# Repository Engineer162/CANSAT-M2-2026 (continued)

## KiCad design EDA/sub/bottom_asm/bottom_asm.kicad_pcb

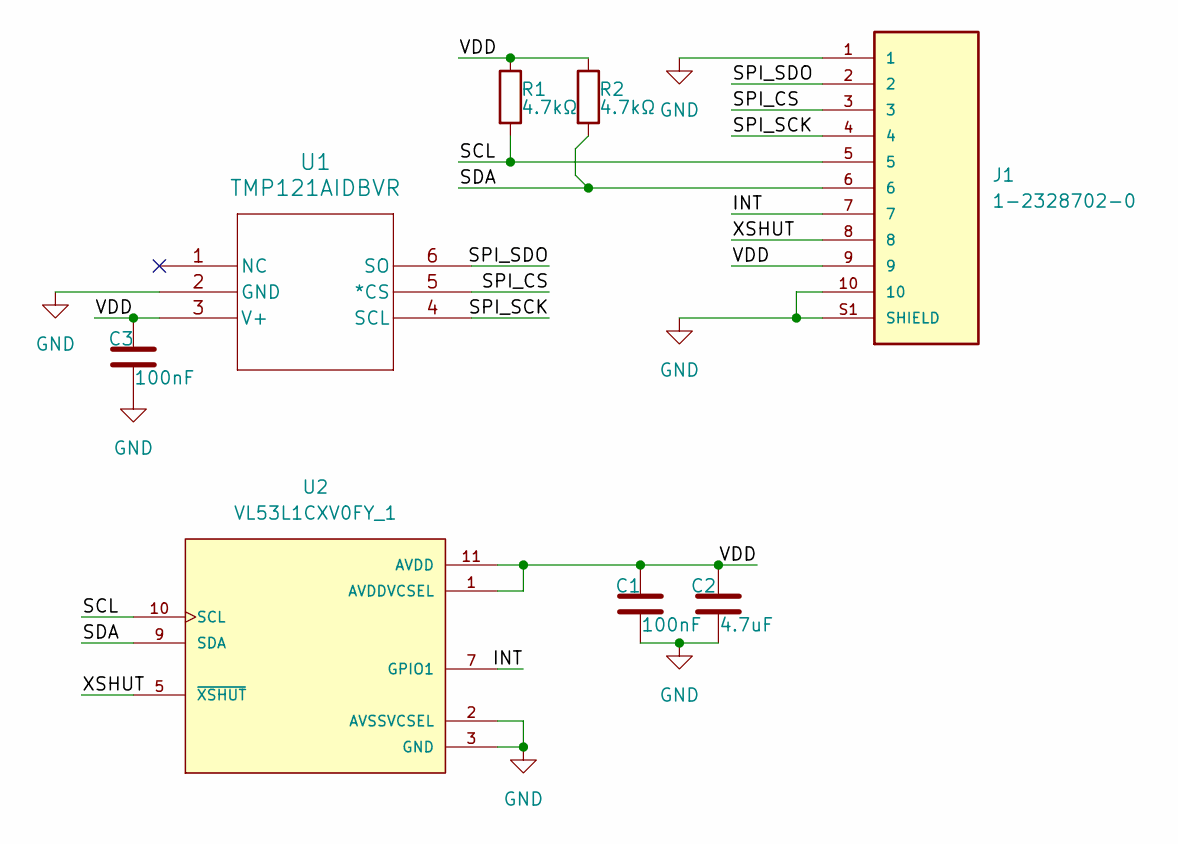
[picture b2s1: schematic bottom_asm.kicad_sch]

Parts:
C1, C3: 100nF; C_0402_1005Metric; Manufacturer Part CL05B104KP5NNNC
C2: 4.7uF; C_0603_1608Metric; Manufacturer Part CL10A475KP8NNNC
J1: 1-2328702-0; TE_1-2328702-0; PARTREV 5; DigiKey_Part_Number A141390CT-ND
R1, R2: 4.7kΩ; R_0402_1005Metric; Manufacturer Part RC0402JR-074K7L
U1: TMP121AIDBVR; DBV6; Manufacturer Part TMP121AIDBVR
U2: VL53L1CXV0FY_1; SENSOR_VL53L1CXV0FY_1; PARTREV 2

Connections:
/INT: J1.7, U2.7 (GPIO1)
/SCL: J1.5, R1.2, U2.10 (SCL)
/SDA: J1.6, R2.2, U2.9 (SDA)
/SPI_CS: J1.3, U1.5 (*CS)
/SPI_SCK: J1.4, U1.4 (SCL)
/SPI_SDO: J1.2, U1.6 (SO)
/VDD: C1.1, C2.1, C3.1, J1.9, R1.1, R2.1, U1.3 (V+), U2.1 (AVDDVCSEL), U2.11 (AVDD)
/XSHUT: J1.8, U2.5 (~XSHUT)
GND: C1.2, C2.2, C3.2, J1.1, J1.10, J1.S1 (SHIELD), J1.S2 (SHIELD), U1.2 (GND), U2.2 (AVSSVCSEL), U2.3 (GND), U2.4 (GND), U2.6 (GND), U2.12 (GND)

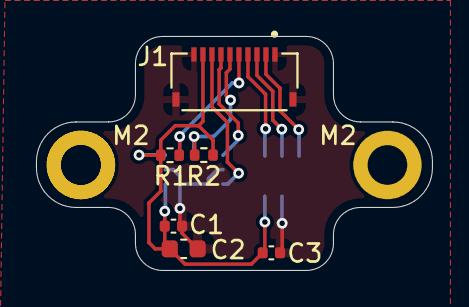
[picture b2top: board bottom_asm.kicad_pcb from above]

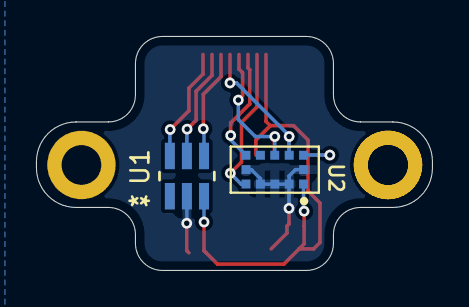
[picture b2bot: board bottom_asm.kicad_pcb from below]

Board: 2 copper layers, 22.0 x 13.0 mm, 10 parts (2 on the bottom side), 9 nets.

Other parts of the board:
M2, M2#2: MountingHole_2.2mm_M2_DIN965_Pad

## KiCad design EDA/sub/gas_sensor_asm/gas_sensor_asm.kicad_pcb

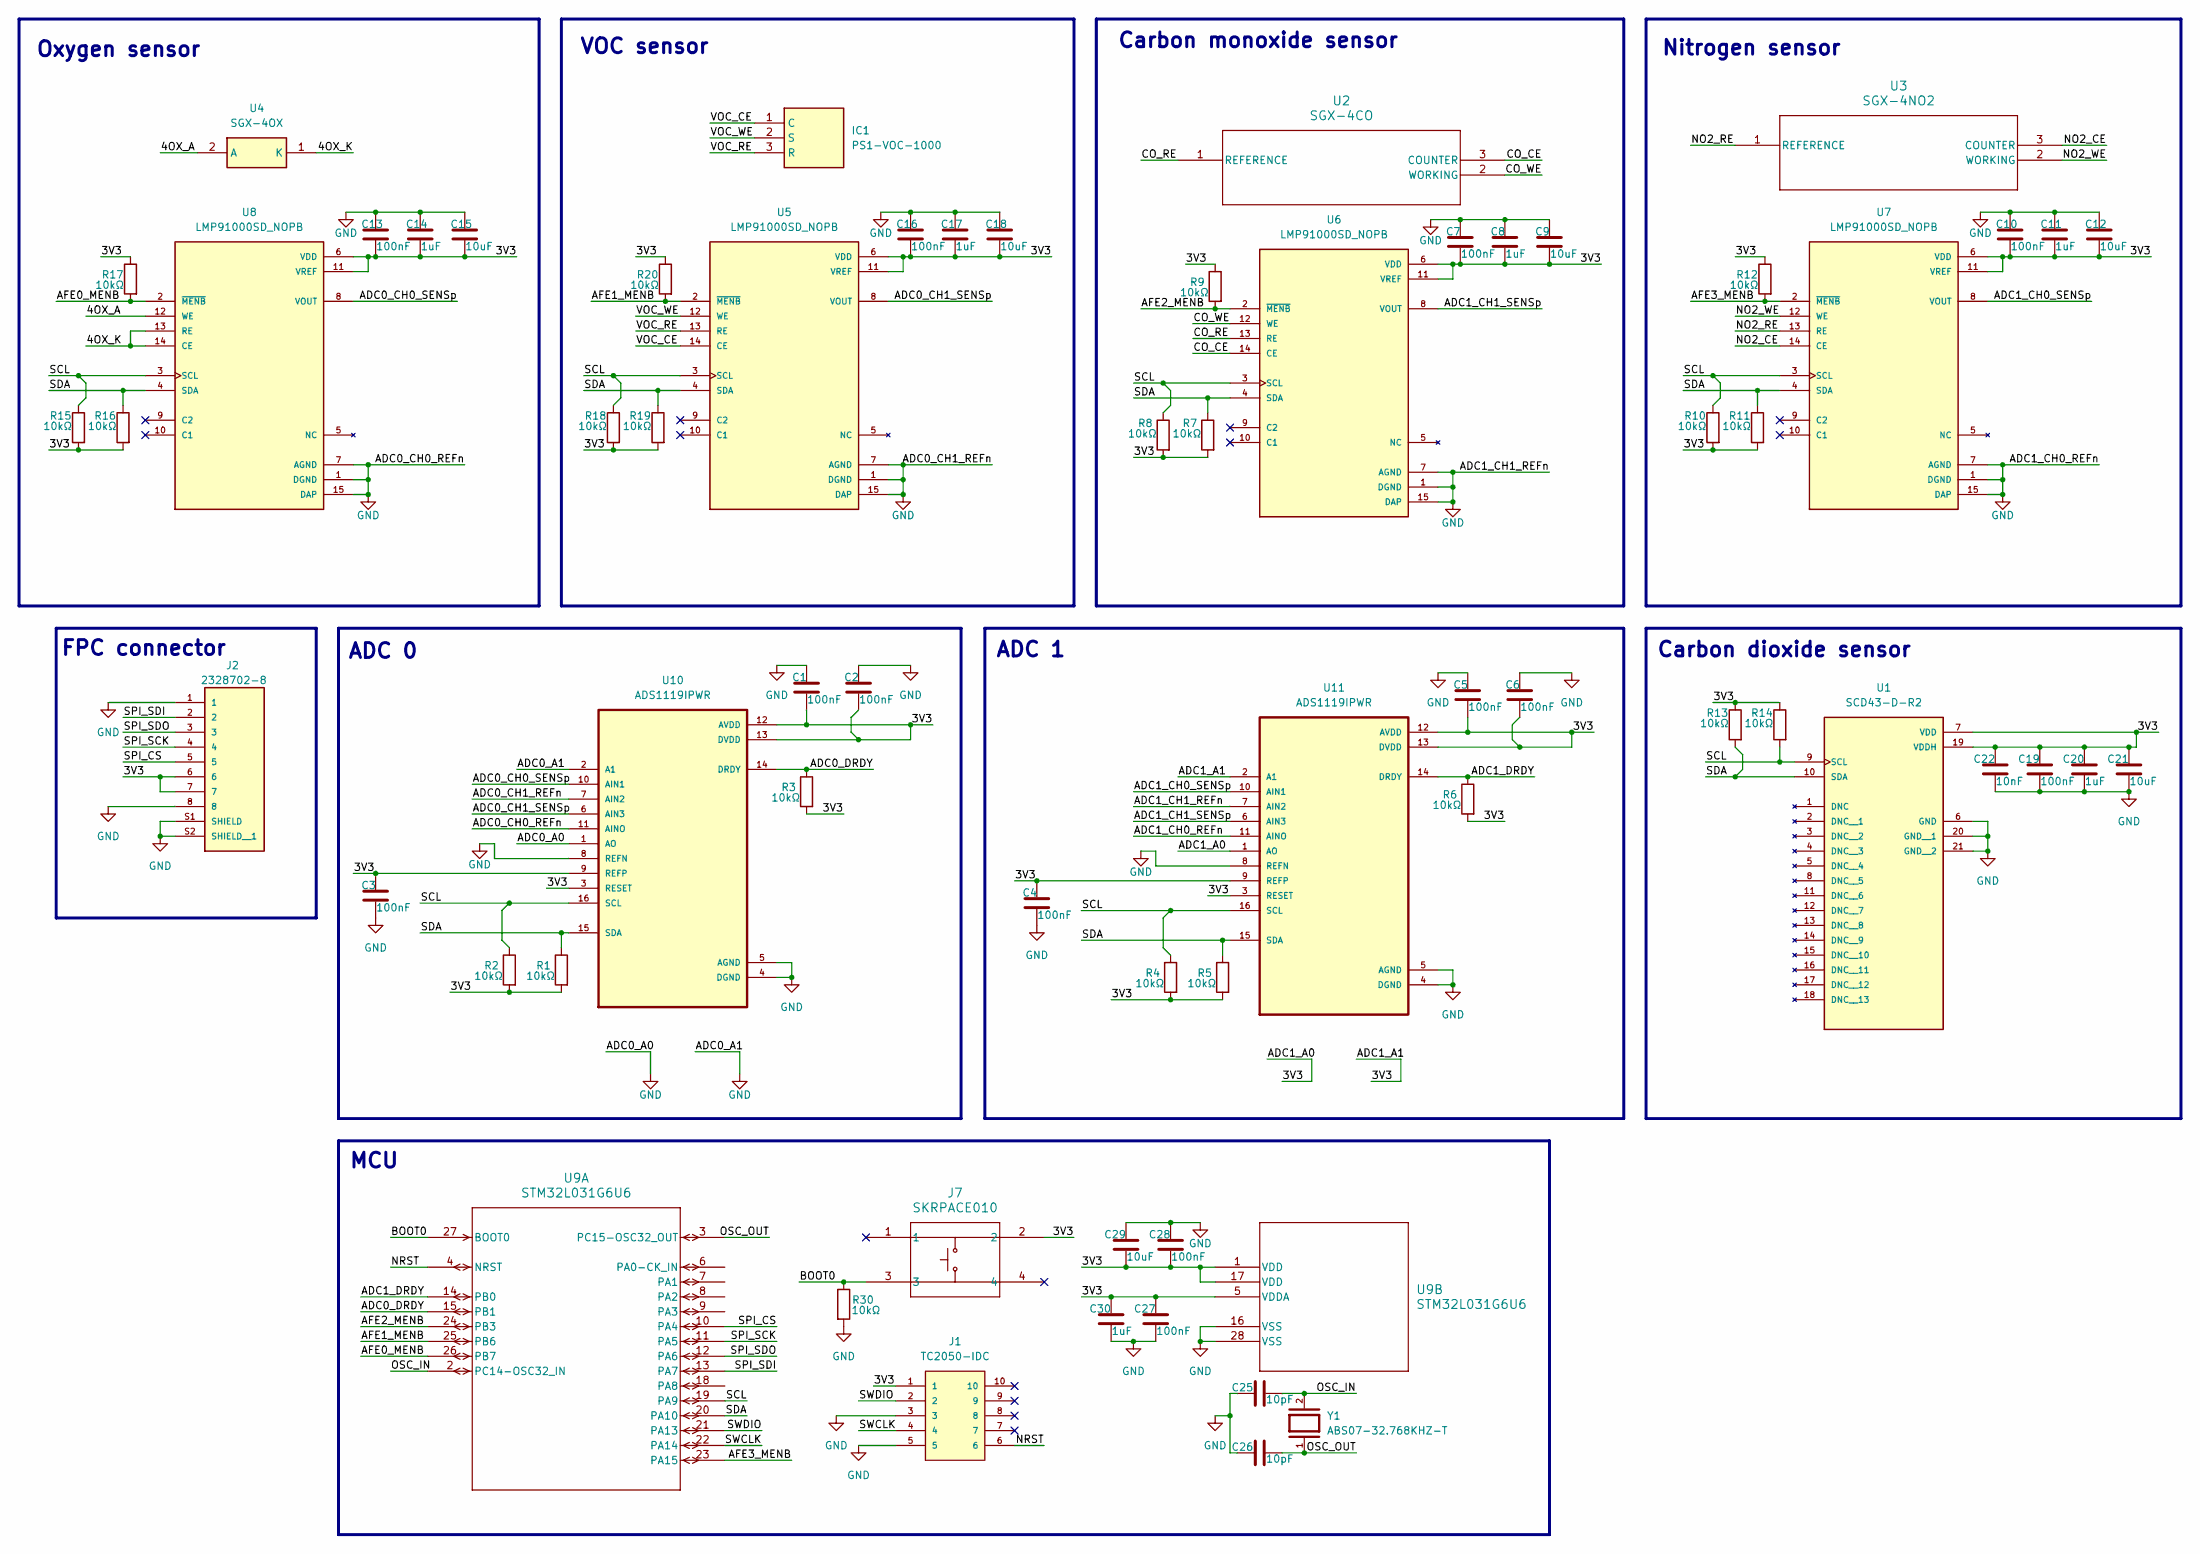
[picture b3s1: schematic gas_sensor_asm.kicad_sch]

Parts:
C1, C2, C3, C4, C5, C6, C7, C10, C13, C16, C19, C27, C28: 100nF; C_0402_1005Metric
C8, C11, C14, C17, C20, C30: 1uF; C_0603_1608Metric
C9, C12, C15, C18, C21, C29: 10uF; C_0603_1608Metric
C22: 10nF; C_0402_1005Metric
C25, C26: 10pF; C_0402_1005Metric
IC1: PS1-VOC-1000; PS1VOC1000; Manufacturer_Part_Number PS1-VOC-1000
J1: TC2050-IDC; TAG-CONNECT_TC2050-IDC; PARTREV A; DigiKey_Part_Number TC2050-IDC-ND
J2: 2328702-8; TE_2328702-8; PARTREV 5
J7: SKRPACE010; SW_SKRPACE010_AAL
R1, R2, R3, R4, R5, R6, R7, R8, R9, R10, R11, R12, R13, R14, R15, R16, R17, R18, R19, R20, R30: 10kΩ; R_0402_1005Metric
U1: SCD43-D-R2; XDCR_SCD43-D-R2; PARTREV 1.2
U2: SGX-4CO
U3: SGX-4NO2
U4: SGX-4OX; SGX4OX; Mouser Part Number 523-SGX-4OX
U5, U6, U7, U8: LMP91000SD_NOPB; SON50P400X400X80-15N; PARTREV I
U9: STM32L031G6U6; UFQFPN28-4x4mm
U10, U11: ADS1119IPWR; SOP65P640X120-16N
Y1: ABS07-32.768KHZ-T; XTAL_ABS07-32.768KHZ-T; PARTREV 08.19.15; DigiKey_Part_Number 535-9542-1-ND

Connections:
/3V3: C1.2, C2.2, C3.1, C4.1, C5.2, C6.2, C7.2, C8.2, C9.2, C10.2, C11.2, C12.2, C13.2, C14.2, C15.2, C16.2, C17.2, C18.2, C19.1, C20.1, C21.1, C22.1, C27.1, C28.2, C29.2, C30.1, J1.1, J2.6, J2.7, J7.2, R1.2, R2.2, R3.2, R4.2, R5.2, R6.2, R7.2, R8.2, R9.1, R10.2, R11.2, R12.1, R13.1, R14.1, R15.2, R16.2, R17.1, R18.2, R19.2, R20.1, U1.7 (VDD), U1.19 (VDDH), U5.6 (VDD), U5.11 (VREF), U6.6 (VDD), U6.11 (VREF), U7.6 (VDD), U7.11 (VREF), U8.6 (VDD), U8.11 (VREF), U9.1 (VDD), U9.5 (VDDA), U9.17 (VDD), U10.3 (RESET), U10.9 (REFP), U10.12 (AVDD), U10.13 (DVDD), U11.1 (AO), U11.2 (A1), U11.3 (RESET), U11.9 (REFP), U11.12 (AVDD), U11.13 (DVDD)
/4OX_A: U4.2 (A), U8.12 (WE)
/4OX_K: U4.1 (K), U8.13 (RE), U8.14 (CE)
/ADC0_CH0_SENSp: U8.8 (VOUT), U10.10 (AIN1)
/ADC0_CH1_SENSp: U5.8 (VOUT), U10.6 (AIN3)
/ADC0_DRDY: R3.1, U9.15 (PB1), U10.14 (DRDY)
/ADC1_CH0_SENSp: U7.8 (VOUT), U11.10 (AIN1)
/ADC1_CH1_SENSp: U6.8 (VOUT), U11.6 (AIN3)
/ADC1_DRDY: R6.1, U9.14 (PB0), U11.14 (DRDY)
/AFE0_MENB: R17.2, U8.2 (~MENB), U9.26 (PB7)
/AFE1_MENB: R20.2, U5.2 (~MENB), U9.25 (PB6)
/AFE2_MENB: R9.2, U6.2 (~MENB), U9.24 (PB3)
/AFE3_MENB: R12.2, U7.2 (~MENB), U9.23 (PA15)
/BOOT0: J7.3, R30.1, U9.27 (BOOT0)
/CO_CE: U2.3 (COUNTER), U6.14 (CE)
/CO_RE: U2.1 (REFERENCE), U6.13 (RE)
/CO_WE: U2.2 (WORKING), U6.12 (WE)
/NO2_CE: U3.3 (COUNTER), U7.14 (CE)
/NO2_RE: U3.1 (REFERENCE), U7.13 (RE)
/NO2_WE: U3.2 (WORKING), U7.12 (WE)
/NRST: J1.6, U9.4 (NRST)
/OSC_IN: C25.2, U9.2 (PC14-OSC32_IN), Y1.2
/OSC_OUT: C26.2, U9.3 (PC15-OSC32_OUT), Y1.1
/SCL: R2.1, R4.1, R8.1, R10.1, R14.2, R15.1, R18.1, U1.9 (SCL), U5.3 (SCL), U6.3 (SCL), U7.3 (SCL), U8.3 (SCL), U9.19 (PA9), U10.16 (SCL), U11.16 (SCL)
/SDA: R1.1, R5.1, R7.1, R11.1, R13.2, R16.1, R19.1, U1.10 (SDA), U5.4 (SDA), U6.4 (SDA), U7.4 (SDA), U8.4 (SDA), U9.20 (PA10), U10.15 (SDA), U11.15 (SDA)
/SPI_CS: J2.5, U9.10 (PA4)
/SPI_SCK: J2.4, U9.11 (PA5)
/SPI_SDI: J2.2, U9.13 (PA7)
/SPI_SDO: J2.3, U9.12 (PA6)
/SWCLK: J1.4, U9.22 (PA14)
/SWDIO: J1.2, U9.21 (PA13)
/VOC_CE: IC1.1 (C), U5.14 (CE)
/VOC_RE: IC1.3 (R), U5.13 (RE)
/VOC_WE: IC1.2 (S), U5.12 (WE)
GND: C1.1, C2.1, C3.2, C4.2, C5.1, C6.1, C7.1, C8.1, C9.1, C10.1, C11.1, C12.1, C13.1, C14.1, C15.1, C16.1, C17.1, C18.1, C19.2, C20.2, C21.2, C22.2, C25.1, C26.1, C27.2, C28.1, C29.1, C30.2, J1.3, J1.5, J2.1, J2.8, J2.S1 (SHIELD), J2.S2 (SHIELD__1), R30.2, U1.6 (GND), U1.20 (GND__1), U1.21 (GND__2), U5.1 (DGND), U5.7 (AGND), U5.15 (DAP), U6.1 (DGND), U6.7 (AGND), U6.15 (DAP), U7.1 (DGND), U7.7 (AGND), U7.15 (DAP), U8.1 (DGND), U8.7 (AGND), U8.15 (DAP), U9.16 (VSS), U9.28 (VSS), U10.1 (AO), U10.2 (A1), U10.4 (DGND), U10.5 (AGND), U10.7 (AIN2), U10.8 (REFN), U10.11 (AINO), U11.4 (DGND), U11.5 (AGND), U11.7 (AIN2), U11.8 (REFN), U11.11 (AINO)

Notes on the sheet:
Nitrogen sensor
Carbon monoxide sensor
ADC 0
MCU
VOC sensor
FPC connector
Carbon dioxide sensor
ADC 1
Oxygen sensor

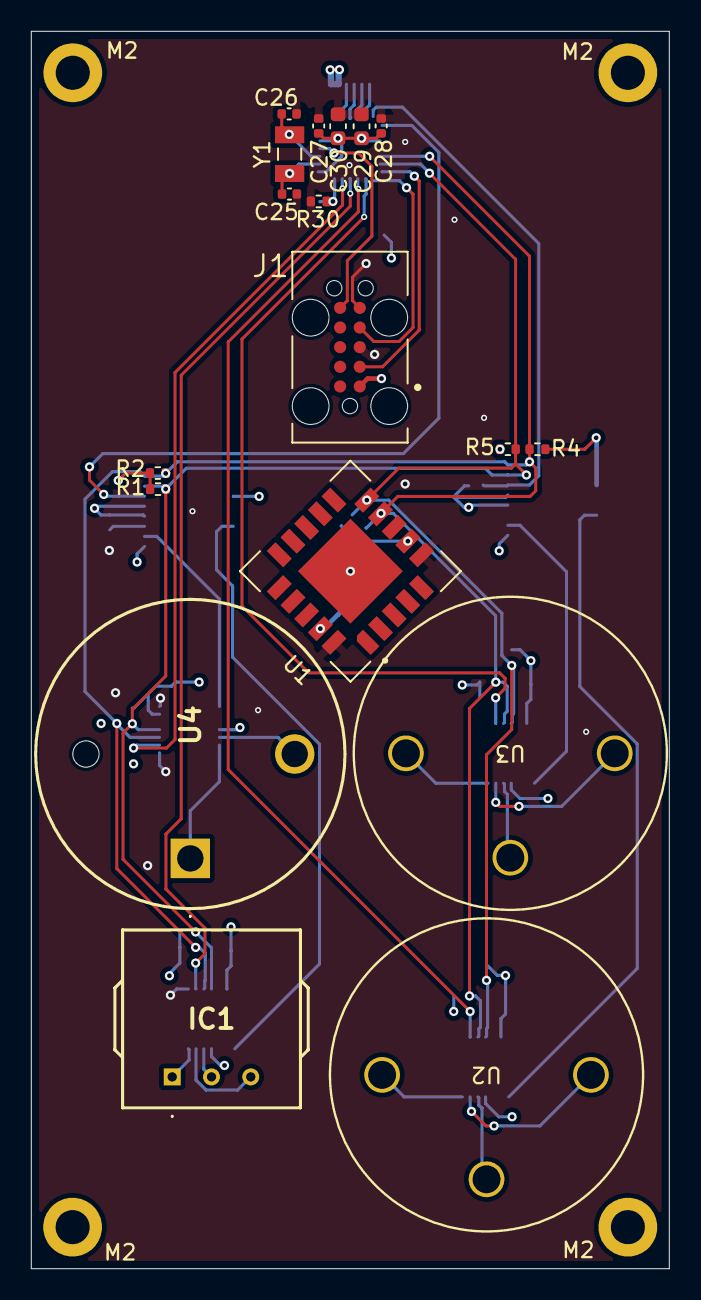
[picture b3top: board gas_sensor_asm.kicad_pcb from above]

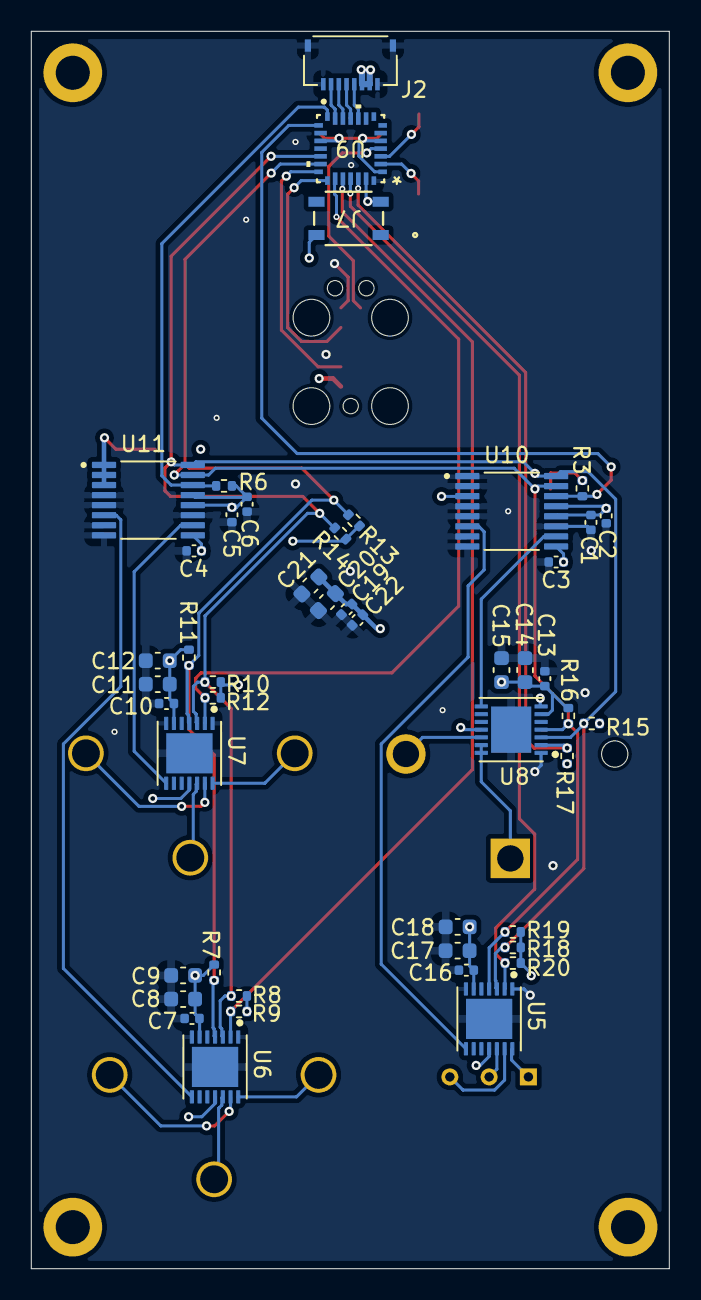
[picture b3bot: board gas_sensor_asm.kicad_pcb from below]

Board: 4 copper layers, 41.2 x 80.0 mm, 69 parts (47 on the bottom side), 35 nets.

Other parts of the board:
M2, M2#2, M2#3, M2#4: MountingHole_2.2mm_M2_DIN965_Pad

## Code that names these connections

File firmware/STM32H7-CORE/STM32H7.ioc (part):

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Mcu.Name=STM32H7S3L8Hx
Mcu.Package=TFBGA225 OCTO SMPS
Mcu.UserName=STM32H7S3L8Hx
PA10.GPIOParameters=PinAttribute
PA10.Mode=Asynchronous
PA10.PinAttribute=Appli
PA10.Signal=USART1_RX
PA13(JTMS/SWDIO).Mode=Serial_Wire
PA13(JTMS/SWDIO).Signal=DEBUG_JTMS-SWDIO
PA14(JTCK/SWCLK).Mode=Serial_Wire
PA14(JTCK/SWCLK).Signal=DEBUG_JTCK-SWCLK
PA3.ContextOwner=Appli
PA3.GPIOParameters=GPIO_Speed,PinState,GPIO_Label,PinAttribute
PA3.GPIO_Label=SPI_CS_IMU
PA3.GPIO_Speed=GPIO_SPEED_FREQ_MEDIUM
PA3.PinAttribute=Appli
PA3.PinState=GPIO_PIN_SET
PA3.Signal=GPIO_Output
PA4.ContextOwner=Appli
PA4.GPIOParameters=GPIO_Label,PinAttribute
PA4.GPIO_Label=IMU_INT1
PA4.PinAttribute=Appli
PA4.Signal=GPXTI4
PA5.ContextOwner=Appli
PA5.GPIOParameters=GPIO_Label,PinAttribute
PA5.GPIO_Label=IMU_INT2
PA5.PinAttribute=Appli
PA5.Signal=GPXTI5
PA6.GPIOParameters=PinAttribute
PA6.Mode=Full_Duplex_Master
PA6.PinAttribute=Appli
PA6.Signal=SPI1_MISO
PA9.GPIOParameters=PinAttribute
PA9.Mode=Asynchronous
PA9.PinAttribute=Appli
PA9.Signal=USART1_TX
PB1.ContextOwner=Appli
PB1.GPIOParameters=GPIO_Label,PinAttribute
PB1.GPIO_Label=GNSS_PPS
PB1.PinAttribute=Appli
PB1.Signal=GPXTI1
PB13.ContextOwner=Appli
PB13.GPIOParameters=GPIO_Label,PinAttribute
PB13.GPIO_Label=ToF_XSHUT
PB13.PinAttribute=Appli
PB13.Signal=GPIO_Output
PB3(JTDO/TRACESWO).GPIOParameters=PinAttribute
PB3(JTDO/TRACESWO).Mode=Full_Duplex_Master
PB3(JTDO/TRACESWO).PinAttribute=Appli
PB3(JTDO/TRACESWO).Signal=SPI3_SCK
PB4(NJTRST).GPIOParameters=PinAttribute
PB4(NJTRST).Mode=Full_Duplex_Master
PB4(NJTRST).PinAttribute=Appli
PB4(NJTRST).Signal=SPI3_MISO
PB5.GPIOParameters=PinAttribute
PB5.Mode=Full_Duplex_Master
PB5.PinAttribute=Appli
PB5.Signal=SPI3_MOSI
PB7.ContextOwner=Appli
PB7.GPIOParameters=GPIO_Speed,GPIO_Label,PinAttribute
PB7.GPIO_Label=SPI_CS_PWR-MCU
PB7.GPIO_Speed=GPIO_SPEED_FREQ_MEDIUM
PB7.PinAttribute=Appli
PB7.Signal=GPIO_Output
PC1.GPIOParameters=PinAttribute
PC1.Mode=Full_Duplex_Master
PC1.PinAttribute=Appli
PC1.Signal=SPI2_MOSI
PC10.GPIOParameters=PinAttribute
PC10.Mode=SD_4_bits_Wide_bus
PC10.PinAttribute=Appli
PC10.Signal=SDMMC1_D2
PC11.GPIOParameters=PinAttribute
PC11.Mode=SD_4_bits_Wide_bus
PC11.PinAttribute=Appli
PC11.Signal=SDMMC1_D3
PC12.GPIOParameters=PinAttribute
PC12.Mode=SD_4_bits_Wide_bus
PC12.PinAttribute=Appli
PC12.Signal=SDMMC1_CK
PC14-OSC32_IN(OSC32_IN).Mode=LSE-External-Oscillator
PC14-OSC32_IN(OSC32_IN).Signal=RCC_OSC32_IN
PC15-OSC32_OUT(OSC32_OUT).Mode=LSE-External-Oscillator
PC15-OSC32_OUT(OSC32_OUT).Signal=RCC_OSC32_OUT
PC2.GPIOParameters=PinAttribute
PC2.Mode=Full_Duplex_Master
PC2.PinAttribute=Appli
PC2.Signal=SPI2_MISO
PC5.GPIOParameters=GPIO_Label,PinAttribute
PC5.GPIO_Label=GNSS_EN
PC5.PinAttribute=Free
PC5.Signal=GPIO_Output
PC8.GPIOParameters=PinAttribute
PC8.Mode=SD_4_bits_Wide_bus
PC8.PinAttribute=Appli
PC8.Signal=SDMMC1_D0
PC9.GPIOParameters=PinAttribute
PC9.Mode=SD_4_bits_Wide_bus
PC9.PinAttribute=Appli
PC9.Signal=SDMMC1_D1
PD11.ContextOwner=Appli
PD11.GPIOParameters=GPIO_Speed,PinState,GPIO_Label,PinAttribute
PD11.GPIO_Label=SPI_CS_BAR
PD11.GPIO_Speed=GPIO_SPEED_FREQ_MEDIUM
PD11.PinAttribute=Appli
PD11.PinState=GPIO_PIN_SET
PD11.Signal=GPIO_Output
PD12.ContextOwner=Appli
PD12.GPIOParameters=GPIO_Speed,PinState,GPIO_Label,PinAttribute
PD12.GPIO_Label=SPI_CS_MAG
PD12.GPIO_Speed=GPIO_SPEED_FREQ_MEDIUM
PD12.PinAttribute=Appli
PD12.PinState=GPIO_PIN_SET
PD12.Signal=GPIO_Output
PD13.ContextOwner=Appli
PD13.GPIOParameters=GPIO_Label,GPIO_ModeDefaultEXTI,PinAttribute
PD13.GPIO_Label=ToF_INT
PD13.GPIO_ModeDefaultEXTI=GPIO_MODE_IT_FALLING
PD13.PinAttribute=Appli
PD13.Signal=GPXTI13
PD14.ContextOwner=Appli
PD14.GPIOParameters=GPIO_Speed,GPIO_Label,PinAttribute
PD14.GPIO_Label=SPI_CS_TMP_IN
PD14.GPIO_Speed=GPIO_SPEED_FREQ_MEDIUM
PD14.PinAttribute=Appli
PD14.Signal=GPIO_Output
PD15.ContextOwner=Appli
PD15.GPIOParameters=GPIO_Speed,PinState,GPIO_Label,PinAttribute
PD15.GPIO_Label=SPI_CS_TMP_OUT
PD15.GPIO_Speed=GPIO_SPEED_FREQ_MEDIUM
PD15.PinAttribute=Appli
PD15.PinState=GPIO_PIN_SET
PD15.Signal=GPIO_Output
PD2.GPIOParameters=PinAttribute
PD2.Mode=SD_4_bits_Wide_bus
PD2.PinAttribute=Appli
PD2.Signal=SDMMC1_CMD
PD3.GPIOParameters=PinAttribute
PD3.Mode=Full_Duplex_Master
PD3.PinAttribute=Appli
PD3.Signal=SPI2_SCK
PD5.GPIOParameters=PinAttribute
PD5.Mode=Asynchronous
PD5.PinAttribute=Appli
PD5.Signal=USART2_TX
PD6.GPIOParameters=PinAttribute
PD6.Mode=Asynchronous
PD6.PinAttribute=Appli
PD6.Signal=USART2_RX
PD7.GPIOParameters=PinAttribute
PD7.Mode=Full_Duplex_Master
PD7.PinAttribute=Appli
PD7.Signal=SPI1_MOSI
PD8.ContextOwner=Appli
PD8.GPIOParameters=GPIO_Label,PinAttribute
PD8.GPIO_Label=BAR_INT
PD8.PinAttribute=Appli
PD8.Signal=GPXTI8
PD9.ContextOwner=Appli
PD9.GPIOParameters=GPIO_Label,PinAttribute
PD9.GPIO_Label=MAG_INT
PD9.PinAttribute=Appli
PD9.Signal=GPXTI9
PE10.GPIOParameters=GPIO_Label,PinAttribute
PE10.GPIO_Label=SPI5_RF_CS
PE10.PinAttribute=Free
PE10.Signal=GPIO_Output
PF0.GPIOParameters=PinAttribute
PF0.Mode=I2C
PF0.PinAttribute=Appli
PF0.Signal=I2C2_SDA
PF1.GPIOParameters=PinAttribute
PF1.Mode=I2C
PF1.PinAttribute=Appli
PF1.Signal=I2C2_SCL
PF13.ContextOwner=Appli
PF13.GPIOParameters=GPIO_Label,PinAttribute
PF13.GPIO_Label=GNSS_RST
PF13.PinAttribute=Appli
PF13.Signal=GPIO_Output
PF14.GPIOParameters=GPIO_Label,PinAttribute
PF14.GPIO_Label=RF_INT
PF14.PinAttribute=Free
PF14.Signal=GPXTI14
PF7.GPIOParameters=PinAttribute
PF7.Mode=Full_Duplex_Master
PF7.PinAttribute=Appli
PF7.Signal=SPI5_SCK
PG11.GPIOParameters=PinAttribute
PG11.Mode=Full_Duplex_Master
PG11.PinAttribute=Appli
PG11.Signal=SPI1_SCK
PG12.GPIOParameters=PinAttribute
PG12.Mode=Full_Duplex_Master
PG12.PinAttribute=Appli
PG12.Signal=SPI6_MISO
PG13.GPIOParameters=PinAttribute
PG13.Mode=Full_Duplex_Master
PG13.PinAttribute=Appli
PG13.Signal=SPI6_SCK
PG14.GPIOParameters=PinAttribute
PG14.Mode=Full_Duplex_Master
PG14.PinAttribute=Appli
PG14.Signal=SPI6_MOSI
PG15.ContextOwner=Appli
PG15.GPIOParameters=GPIO_Speed,GPIO_Label,PinAttribute
PG15.GPIO_Label=SPI_CS_EXT_SENS
PG15.GPIO_Speed=GPIO_SPEED_FREQ_MEDIUM
PG15.PinAttribute=Appli
PG15.Signal=GPIO_Output
PH0-OSC_IN(PH0).Mode=HSE-External-Oscillator
PH0-OSC_IN(PH0).Signal=RCC_OSC_IN
PH1-OSC_OUT(PH1).Mode=HSE-External-Oscillator
PH1-OSC_OUT(PH1).Signal=RCC_OSC_OUT
RCC.HSE_VALUE=25000000
RCC.SYSCLKFreq_VALUE=600000000
RCC.SYSCLKSource=RCC_SYSCLKSOURCE_PLLCLK
board=custom

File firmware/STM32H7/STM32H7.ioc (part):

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Mcu.Name=STM32H7S3L8Hx
Mcu.Package=TFBGA225 OCTO SMPS
Mcu.UserName=STM32H7S3L8Hx
PA10.GPIOParameters=PinAttribute
PA10.PinAttribute=Appli
PA10.Signal=FMC_D2_DA2
PA11.GPIOParameters=PinAttribute
PA11.PinAttribute=Appli
PA11.Signal=FMC_D1_DA1
PA12.GPIOParameters=PinAttribute
PA12.PinAttribute=Appli
PA12.Signal=FMC_D0_DA0
PA13(JTMS/SWDIO).Mode=Serial_Wire
PA13(JTMS/SWDIO).Signal=DEBUG_JTMS-SWDIO
PA14(JTCK/SWCLK).Mode=Serial_Wire
PA14(JTCK/SWCLK).Signal=DEBUG_JTCK-SWCLK
PA3.ContextOwner=Appli
PA3.GPIOParameters=GPIO_Speed,PinState,GPIO_Label,PinAttribute
PA3.GPIO_Label=SPI_CS_IMU
PA3.GPIO_Speed=GPIO_SPEED_FREQ_MEDIUM
PA3.PinAttribute=Appli
PA3.PinState=GPIO_PIN_SET
PA3.Signal=GPIO_Output
PA4.ContextOwner=Appli
PA4.GPIOParameters=GPIO_Label,PinAttribute
PA4.GPIO_Label=IMU_INT1
PA4.PinAttribute=Appli
PA4.Signal=GPXTI4
PA5.ContextOwner=Appli
PA5.GPIOParameters=GPIO_Label,PinAttribute
PA5.GPIO_Label=IMU_INT2
PA5.PinAttribute=Appli
PA5.Signal=GPXTI5
PA6.GPIOParameters=PinAttribute
PA6.Mode=Full_Duplex_Master
PA6.PinAttribute=Appli
PA6.Signal=SPI1_MISO
PA8.GPIOParameters=PinAttribute
PA8.PinAttribute=Appli
PA8.Signal=FMC_D4_DA4
PA9.GPIOParameters=PinAttribute
PA9.PinAttribute=Appli
PA9.Signal=FMC_D3_DA3
PB10.GPIOParameters=PinAttribute
PB10.Mode=I2C
PB10.PinAttribute=Appli
PB10.Signal=I2C2_SCL
PB11.GPIOParameters=PinAttribute
PB11.Mode=I2C
PB11.PinAttribute=Appli
PB11.Signal=I2C2_SDA
PB13.ContextOwner=Appli
PB13.GPIOParameters=GPIO_Label,PinAttribute
PB13.GPIO_Label=ToF_XSHUT
PB13.PinAttribute=Appli
PB13.Signal=GPIO_Output
PB14.GPIOParameters=PinAttribute
PB14.Mode=Full_Duplex_Master
PB14.PinAttribute=Appli
PB14.Signal=SPI2_MISO
PB15.GPIOParameters=PinAttribute
PB15.Mode=Full_Duplex_Master
PB15.PinAttribute=Appli
PB15.Signal=SPI2_MOSI
PB3(JTDO/TRACESWO).GPIOParameters=PinAttribute
PB3(JTDO/TRACESWO).Mode=Full_Duplex_Master
PB3(JTDO/TRACESWO).PinAttribute=Appli
PB3(JTDO/TRACESWO).Signal=SPI3_SCK
PB4(NJTRST).GPIOParameters=PinAttribute
PB4(NJTRST).Mode=Full_Duplex_Master
PB4(NJTRST).PinAttribute=Appli
PB4(NJTRST).Signal=SPI3_MISO
PB5.GPIOParameters=PinAttribute
PB5.Mode=Full_Duplex_Master
PB5.PinAttribute=Appli
PB5.Signal=SPI1_MOSI
PB7.ContextOwner=Appli
PB7.GPIOParameters=GPIO_Speed,GPIO_Label,PinAttribute
PB7.GPIO_Label=SPI_CS_PWR-MCU
PB7.GPIO_Speed=GPIO_SPEED_FREQ_MEDIUM
PB7.PinAttribute=Appli
PB7.Signal=GPIO_Output
PC0.GPIOParameters=PinAttribute
PC0.PinAttribute=Appli
PC0.Signal=FMC_NBL1
PC1.GPIOParameters=PinAttribute
PC1.PinAttribute=Appli
PC1.Signal=FMC_A0
PC10.GPIOParameters=PinAttribute
PC10.Mode=SD_4_bits_Wide_bus
PC10.PinAttribute=Appli
PC10.Signal=SDMMC1_D2
PC11.GPIOParameters=PinAttribute
PC11.Mode=SD_4_bits_Wide_bus
PC11.PinAttribute=Appli
PC11.Signal=SDMMC1_D3
PC12.GPIOParameters=PinAttribute
PC12.Mode=SD_4_bits_Wide_bus
PC12.PinAttribute=Appli
PC12.Signal=SDMMC1_CK
PC14-OSC32_IN(OSC32_IN).Mode=LSE-External-Oscillator
PC14-OSC32_IN(OSC32_IN).Signal=RCC_OSC32_IN
PC15-OSC32_OUT(OSC32_OUT).Mode=LSE-External-Oscillator
PC15-OSC32_OUT(OSC32_OUT).Signal=RCC_OSC32_OUT
PC2.GPIOParameters=PinAttribute
PC2.PinAttribute=Appli
PC2.Signal=FMC_A1
PC3.GPIOParameters=PinAttribute
PC3.PinAttribute=Appli
PC3.Signal=FMC_A2
PC4.GPIOParameters=PinAttribute
PC4.PinAttribute=Appli
PC4.Signal=FMC_A3
PC5.GPIOParameters=PinAttribute
PC5.PinAttribute=Appli
PC5.Signal=FMC_A5
PC8.GPIOParameters=PinAttribute
PC8.Mode=SD_4_bits_Wide_bus
PC8.PinAttribute=Appli
PC8.Signal=SDMMC1_D0
PC9.GPIOParameters=PinAttribute
PC9.Mode=SD_4_bits_Wide_bus
PC9.PinAttribute=Appli
PC9.Signal=SDMMC1_D1
PD0.GPIOParameters=PinAttribute
PD0.PinAttribute=Appli
PD0.Signal=FMC_A6
PD1.GPIOParameters=PinAttribute
PD1.PinAttribute=Appli
PD1.Signal=FMC_A7
PD11.ContextOwner=Appli
PD11.GPIOParameters=GPIO_Speed,PinState,GPIO_Label,PinAttribute
PD11.GPIO_Label=SPI_CS_BAR
PD11.GPIO_Speed=GPIO_SPEED_FREQ_MEDIUM
PD11.PinAttribute=Appli
PD11.PinState=GPIO_PIN_SET
PD11.Signal=GPIO_Output
PD12.ContextOwner=Appli
PD12.GPIOParameters=GPIO_Speed,PinState,GPIO_Label,PinAttribute
PD12.GPIO_Label=SPI_CS_MAG
PD12.GPIO_Speed=GPIO_SPEED_FREQ_MEDIUM
PD12.PinAttribute=Appli
PD12.PinState=GPIO_PIN_SET
PD12.Signal=GPIO_Output
PD13.ContextOwner=Appli
PD13.GPIOParameters=GPIO_Label,GPIO_ModeDefaultEXTI,PinAttribute
PD13.GPIO_Label=ToF_INT
PD13.GPIO_ModeDefaultEXTI=GPIO_MODE_IT_FALLING
PD13.PinAttribute=Appli
PD13.Signal=GPXTI13
PD14.ContextOwner=Appli
PD14.GPIOParameters=GPIO_Speed,GPIO_Label,PinAttribute
PD14.GPIO_Label=SPI_CS_TMP_IN
PD14.GPIO_Speed=GPIO_SPEED_FREQ_MEDIUM
PD14.PinAttribute=Appli
PD14.Signal=GPIO_Output
PD15.ContextOwner=Appli
PD15.GPIOParameters=GPIO_Speed,PinState,GPIO_Label,PinAttribute
PD15.GPIO_Label=SPI_CS_TMP_OUT
PD15.GPIO_Speed=GPIO_SPEED_FREQ_MEDIUM
PD15.PinAttribute=Appli
PD15.PinState=GPIO_PIN_SET
PD15.Signal=GPIO_Output
PD2.GPIOParameters=PinAttribute
PD2.Mode=SD_4_bits_Wide_bus
PD2.PinAttribute=Appli
PD2.Signal=SDMMC1_CMD
PD3.GPIOParameters=PinAttribute
PD3.Mode=Full_Duplex_Master
PD3.PinAttribute=Appli
PD3.Signal=SPI2_SCK
PD6.GPIOParameters=PinAttribute
PD6.Mode=Full_Duplex_Master
PD6.PinAttribute=Appli
PD6.Signal=SPI3_MOSI
PD7.GPIOParameters=PinAttribute
PD7.PinAttribute=Appli
PD7.Signal=FMC_D8_DA8
PD8.ContextOwner=Appli
PD8.GPIOParameters=GPIO_Label,PinAttribute
PD8.GPIO_Label=BAR_INT
PD8.PinAttribute=Appli
PD8.Signal=GPXTI8
PD9.ContextOwner=Appli
PD9.GPIOParameters=GPIO_Label,PinAttribute
PD9.GPIO_Label=MAG_INT
PD9.PinAttribute=Appli
PD9.Signal=GPXTI9
PE0.GPIOParameters=PinAttribute
PE0.PinAttribute=Appli
PE0.Signal=FMC_D9_DA9
PE1.GPIOParameters=PinAttribute
PE1.PinAttribute=Appli
PE1.Signal=FMC_D10_DA10
PE10.GPIOParameters=PinAttribute
PE10.PinAttribute=Appli
PE10.Signal=FMC_A15_BA1
PE11.GPIOParameters=PinAttribute
PE11.PinAttribute=Appli
PE11.Signal=FMC_SDNWE
PE12.GPIOParameters=PinAttribute
PE12.PinAttribute=Appli
PE12.Signal=FMC_SDNRAS
PE13.GPIOParameters=PinAttribute
PE13.PinAttribute=Appli
PE13.Signal=FMC_SDNCAS
PE14.GPIOParameters=PinAttribute
PE14.Mode=SdramChipSelect1_1
PE14.PinAttribute=Appli
PE14.Signal=FMC_SDNE0
PE15.GPIOParameters=PinAttribute
PE15.Mode=SdramChipSelect1_1
PE15.PinAttribute=Appli
PE15.Signal=FMC_SDCKE0
PE2.GPIOParameters=PinAttribute
PE2.PinAttribute=Appli
PE2.Signal=FMC_D11_DA11
PE3.GPIOParameters=PinAttribute
PE3.PinAttribute=Appli
PE3.Signal=FMC_D12_DA12
PE4.GPIOParameters=PinAttribute
PE4.PinAttribute=Appli
PE4.Signal=FMC_D13_DA13
PE5.GPIOParameters=PinAttribute
PE5.PinAttribute=Appli
PE5.Signal=FMC_D14_DA14
PE6.GPIOParameters=PinAttribute
PE6.PinAttribute=Appli
PE6.Signal=FMC_D15_DA15
PE7.GPIOParameters=PinAttribute
PE7.PinAttribute=Appli
PE7.Signal=FMC_A4
PE9.GPIOParameters=PinAttribute
PE9.PinAttribute=Appli
PE9.Signal=FMC_A14_BA0
PF0.GPIOParameters=PinAttribute
PF0.PinAttribute=Appli
PF0.Signal=FMC_A8
PF1.GPIOParameters=PinAttribute
PF1.PinAttribute=Appli
PF1.Signal=FMC_A9
PF2.GPIOParameters=PinAttribute
PF2.PinAttribute=Appli
PF2.Signal=FMC_A10
PF3.GPIOParameters=PinAttribute
PF3.PinAttribute=Appli
PF3.Signal=FMC_A11
PG11.GPIOParameters=PinAttribute
PG11.Mode=Full_Duplex_Master
PG11.PinAttribute=Appli
PG11.Signal=SPI1_SCK
PG12.GPIOParameters=PinAttribute
PG12.Mode=Full_Duplex_Master
PG12.PinAttribute=Appli
PG12.Signal=SPI6_MISO
PG13.GPIOParameters=PinAttribute
PG13.Mode=Full_Duplex_Master
PG13.PinAttribute=Appli
PG13.Signal=SPI6_SCK
PG14.GPIOParameters=PinAttribute
PG14.Mode=Full_Duplex_Master
PG14.PinAttribute=Appli
PG14.Signal=SPI6_MOSI
PG15.ContextOwner=Appli
PG15.GPIOParameters=GPIO_Speed,GPIO_Label,PinAttribute
PG15.GPIO_Label=SPI_CS_EXT_SENS
PG15.GPIO_Speed=GPIO_SPEED_FREQ_MEDIUM
PG15.PinAttribute=Appli
PG15.Signal=GPIO_Output
PH0-OSC_IN(PH0).Mode=HSE-External-Oscillator
PH0-OSC_IN(PH0).Signal=RCC_OSC_IN
PH1-OSC_OUT(PH1).Mode=HSE-External-Oscillator
PH1-OSC_OUT(PH1).Signal=RCC_OSC_OUT
RCC.HSE_VALUE=25000000
RCC.SYSCLKFreq_VALUE=600000000
RCC.SYSCLKSource=RCC_SYSCLKSOURCE_PLLCLK
board=custom

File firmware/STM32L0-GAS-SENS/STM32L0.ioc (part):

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Mcu.Name=STM32L031G(4-6)Ux
Mcu.Package=UFQFPN28
Mcu.UserName=STM32L031G6Ux
PA10.Mode=I2C
PA10.Signal=I2C1_SDA
PA13.Mode=Serial_Wire
PA13.Signal=SYS_SWDIO
PA14.Mode=Serial_Wire
PA14.Signal=SYS_SWCLK
PA15.GPIOParameters=GPIO_Speed,GPIO_Label
PA15.GPIO_Label=AFE3_MENB
PA15.GPIO_Speed=GPIO_SPEED_FREQ_MEDIUM
PA15.Signal=GPIO_Output
PA4.Mode=NSS_Signal_Hard_Input
PA4.Signal=SPI1_NSS
PA5.Mode=Full_Duplex_Slave
PA5.Signal=SPI1_SCK
PA6.Mode=Full_Duplex_Slave
PA6.Signal=SPI1_MISO
PA7.Mode=Full_Duplex_Slave
PA7.Signal=SPI1_MOSI
PA9.Mode=I2C
PA9.Signal=I2C1_SCL
PB0.GPIOParameters=GPIO_Label
PB0.GPIO_Label=ADC1_DRDY
PB0.Signal=GPXTI0
PB1.GPIOParameters=GPIO_Label
PB1.GPIO_Label=ADC0_DRDY
PB1.Signal=GPXTI1
PB3.GPIOParameters=GPIO_Speed,GPIO_Label
PB3.GPIO_Label=AFE2_MENB
PB3.GPIO_Speed=GPIO_SPEED_FREQ_MEDIUM
PB3.Signal=GPIO_Output
PB6.GPIOParameters=GPIO_FM6,GPIO_Speed,GPIO_Label
PB6.GPIO_FM6=__NULL
PB6.GPIO_Label=AFE1_MENB
PB6.GPIO_Speed=GPIO_SPEED_FREQ_MEDIUM
PB6.Signal=GPIO_Output
PB7.GPIOParameters=GPIO_Speed,GPIO_Label
PB7.GPIO_Label=AFE0_MENB
PB7.GPIO_Speed=GPIO_SPEED_FREQ_MEDIUM
PB7.Signal=GPIO_Output
PC14-OSC32_IN.Mode=LSE-External-Oscillator
PC14-OSC32_IN.Signal=RCC_OSC32_IN
PC15-OSC32_OUT.Mode=LSE-External-Oscillator
PC15-OSC32_OUT.Signal=RCC_OSC32_OUT
RCC.HSE_VALUE=32000000
RCC.SYSCLKFreq_VALUE=32000000
RCC.SYSCLKSource=RCC_SYSCLKSOURCE_PLLCLK
board=custom

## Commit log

2026-02-06 Added licenses
2026-02-06 Update licensing structure description
2026-02-06 Uploaded sensor schematic
2026-02-06 update README with project overview and sensors
    Added project description and sensor details to README.
2026-03-10 Changed barometer to BOSCH BMP581, and added outside and inside temperature sensors.
2026-03-25 Ported EDA from EasyEDA to KiCad
2026-03-25 Changed STM32 MCU type, and added SDRAM. Micro-SD card slot has also been set up.
2026-03-26 Added USB-C power negotiator and battery charger
2026-03-26 Choose USB-C connector to be used
2026-03-26 Changed PD IC from TPS25750DRJKR to TPS25730DREFR
2026-03-27 added smoothing capacitors to PD IC
2026-03-27 PD negotiator IC wired up in schematic
2026-03-28 Did some scheamtic restruscturing as well as hooked up SDRAM and Micro-SD to STM32 core. Additional low power STM32 has also been added to power control. Firmware .IOC files have also been added for 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
2026-03-30 Project restructure, and added a bottom assembly PCB.
2026-03-30 Assigned CS and INT from sensors, and added SWD to PWR-MCU and CORE-MCU
2026-04-01 Update project title in README
2026-04-20 Uploaded work
2026-04-20 Added gas sensor sub-board
2026-04-21 Finished gas sensor PCB, and added connector for it on main PCB
2026-04-22 Added GNSS and SIM800L
2026-04-26 Worked on SDRAM
2026-04-26 Made main branch not include SDRAM
2026-05-05 PCB done
